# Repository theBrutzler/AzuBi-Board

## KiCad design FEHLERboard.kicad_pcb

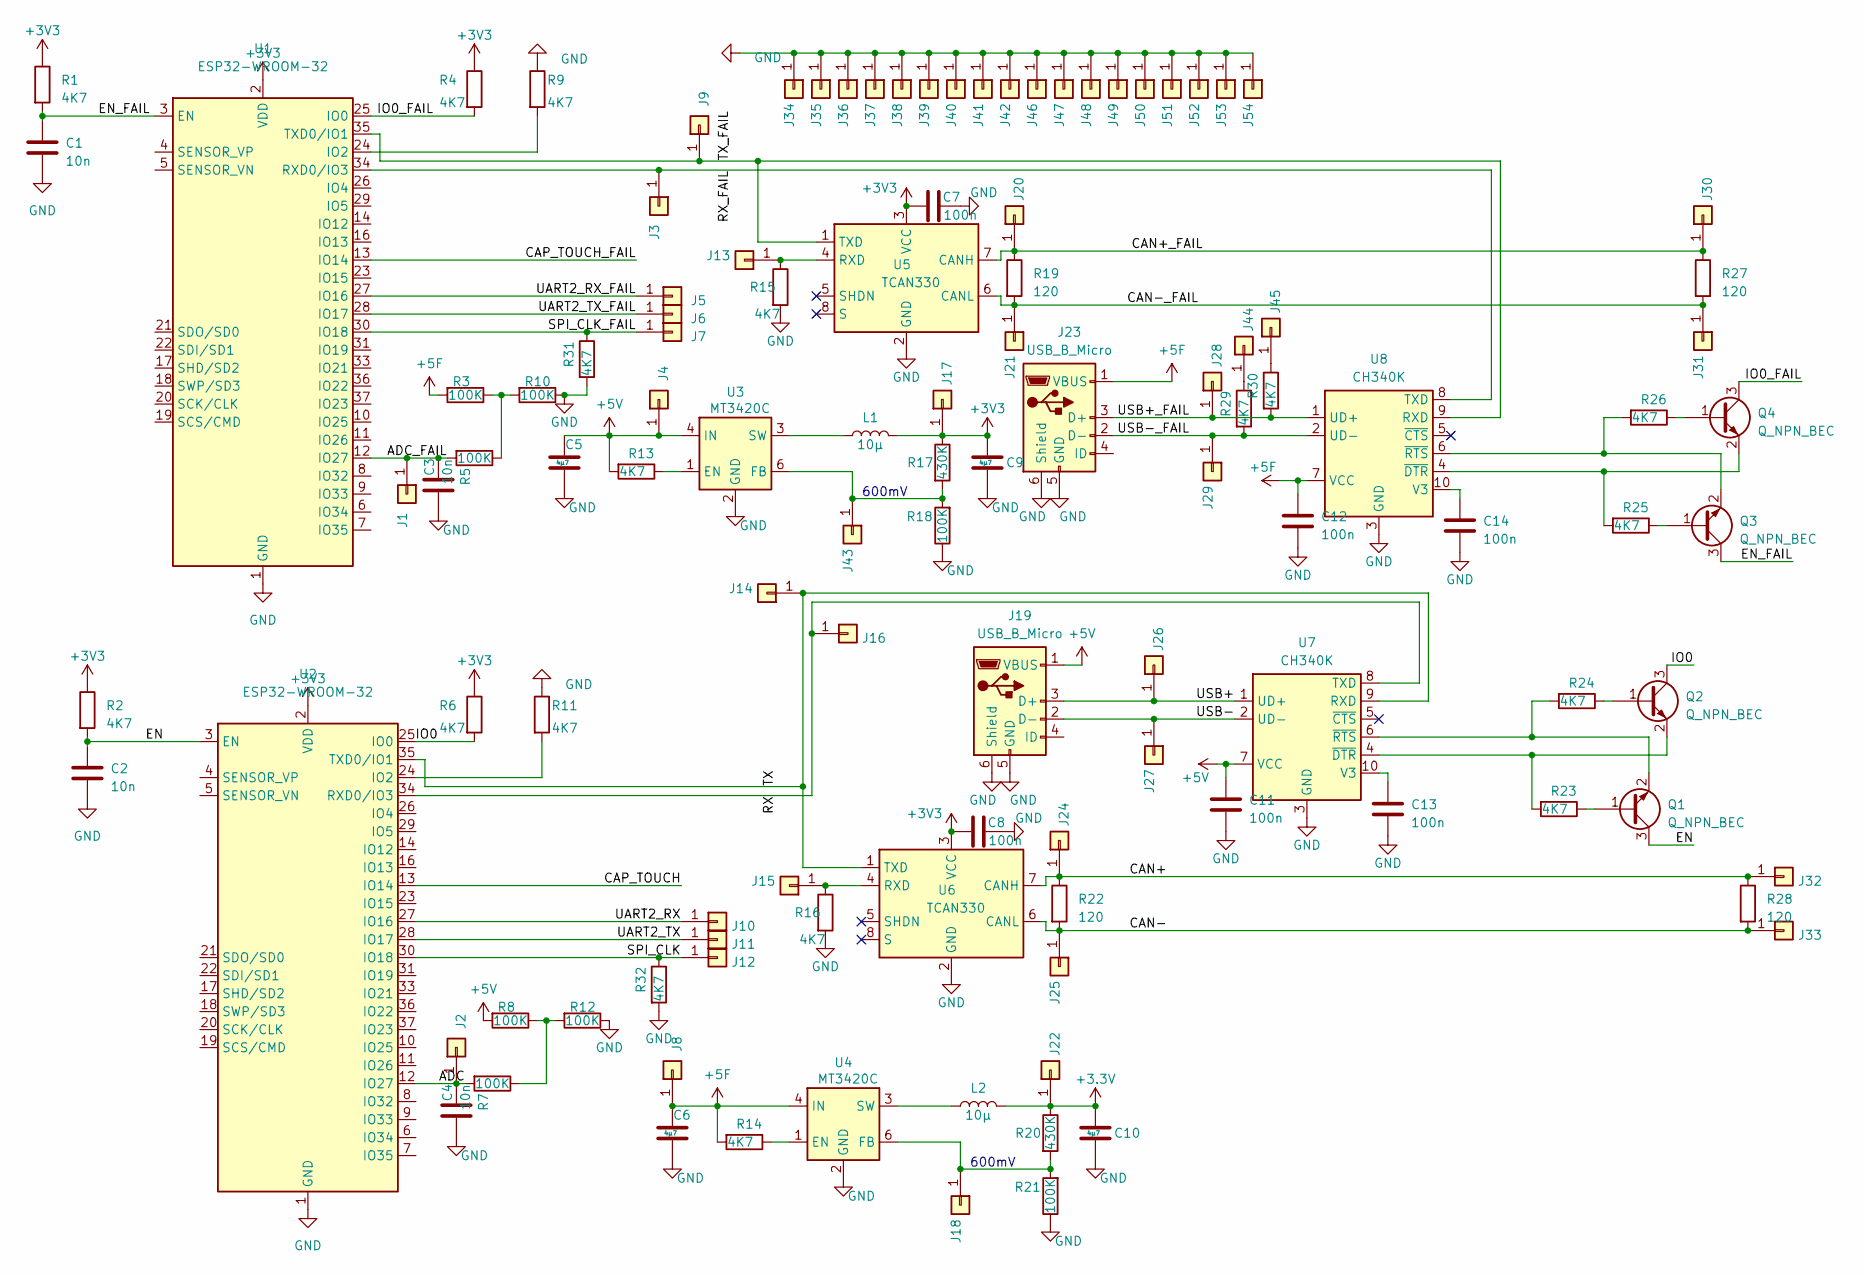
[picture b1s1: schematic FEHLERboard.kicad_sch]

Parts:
C1, C2, C3, C4: 10n; C_0603_1608Metric
C5, C6, C9, C10: 4µ7; C_0603_1608Metric; LCSC C415373
C7, C8, C11, C12, C13, C14: 100n; C_0603_1608Metric
J1, J2, J3, J4, J5, J6, J7, J8, J9, J10, J11, J12, J13, J14, J15, J16, J17, J18, J20, J21, J22, J24, J25, J26, J27, J28, J29, J30, J31, J32, J33, J43, J44, J45: Conn_01x01; TestPoint_THTPad_D1.5mm_Drill0.7mm
J19, J23: USB_B_Micro; USB_Micro-B_Amphenol_10103594-0001LF_Horizontal
J34, J35, J36, J37, J38, J39, J40, J41, J42, J46, J47, J48, J49, J50, J51, J52, J53, J54: Conn_01x01; TestPoint_THTPad_1.5x1.5mm_Drill0.7mm
L1, L2: 10µ; L_Bourns-SRN4018; LCSC C520273
Q1, Q2, Q3, Q4: Q_NPN_BEC; SOT-23; LCSC C181167
R1, R2, R4, R6, R9, R11, R15, R16: 4K7; R_0603_1608Metric
R3, R5, R7, R8, R10, R12, R18, R21: 100K; R_0603_1608Metric; LCSC C15458
R13, R14, R23, R24, R25, R26, R29, R30, R31, R32: 4K7; R_0603_1608Metric; LCSC C105428
R17, R20: 430K; R_0603_1608Metric; LCSC C170597
R19, R22, R27, R28: 120; R_0603_1608Metric
U1, U2: ESP32-WROOM-32
U3, U4: MT3420C; SOT-23-6; LCSC C181741
U5, U6: TCAN330; SOIC-8_3.9x4.9mm_P1.27mm
U7, U8: CH340K; SSOP-10_EP1_3.9x4.9mm_P1.00mm; LCSC C968586

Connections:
+5F: C6.1, C12.1, J8.1, J23.1 (VBUS), R3.2, R14.2, U4.4 (IN), U8.7 (VCC)
+5V: C5.1, C11.1, J4.1, J19.1 (VBUS), R8.2, R13.2, U3.4 (IN), U7.7 (VCC)
/ADC: C4.2, J2.1, R7.2, U2.12 (IO27)
/ADC_FAIL: C3.2, J1.1, R5.2, U1.12 (IO27)
/CAN+: J24.1, J32.1, R22.1, R28.1, U6.7 (CANH)
/CAN+_FAIL: J20.1, J30.1, R19.1, R27.1, U5.7 (CANH)
/CAN-: J25.1, J33.1, R22.2, R28.2, U6.6 (CANL)
/CAN-_FAIL: J21.1, J31.1, R19.2, R27.2, U5.6 (CANL)
/CAP_TOUCH: U2.13 (IO14)
/CAP_TOUCH_FAIL: U1.13 (IO14)
/EN: C2.1, Q1.3 (C), R2.2, U2.3 (EN)
/EN_FAIL: C1.1, Q3.3 (C), R1.2, U1.3 (EN)
/IO0: Q2.3 (C), R6.2, U2.25 (IO0)
/IO0_FAIL: Q4.3 (C), R4.2, U1.25 (IO0)
/RX: J16.1, U2.34 (RXD0/IO3), U7.8 (TXD)
/RX_FAIL: J3.1, U1.34 (RXD0/IO3), U8.8 (TXD)
/SPI_CLK: J12.1, R32.1, U2.30 (IO18)
/SPI_CLK_FAIL: J7.1, R31.1, U1.30 (IO18)
/TX: J14.1, U2.35 (TXD0/IO1), U6.1 (TXD), U7.9 (RXD)
/TX_FAIL: J9.1, U1.35 (TXD0/IO1), U5.1 (TXD), U8.9 (RXD)
/UART2_RX: J10.1, U2.27 (IO16)
/UART2_RX_FAIL: J5.1, U1.27 (IO16)
/UART2_TX: J11.1, U2.28 (IO17)
/UART2_TX_FAIL: J6.1, U1.28 (IO17)
/USB+: J19.3 (D+), J26.1, U7.1 (UD+)
/USB+_FAIL: J23.3 (D+), J28.1, R30.2, U8.1 (UD+)
/USB-: J19.2 (D-), J27.1, U7.2 (UD-)
/USB-_FAIL: J23.2 (D-), J29.1, R29.2, U8.2 (UD-)
GND: C1.2, C2.2, C3.1, C4.1, C5.2, C6.2, C7.2, C8.2, C9.2, C10.2, C11.2, C12.2, C13.2, C14.2, J19.5 (GND), J19.6 (Shield), J23.5 (GND), J23.6 (Shield), J34.1, J35.1, J36.1, J37.1, J38.1, J39.1, J40.1, J41.1, J42.1, J46.1, J47.1, J48.1, J49.1, J50.1, J51.1, J52.1, J53.1, J54.1, R9.1, R10.1, R11.1, R12.1, R15.2, R16.2, R18.1, R21.1, R31.2, R32.2, U1.1 (GND), U1.15 (GND), U1.38 (GND), U1.39 (GND), U2.1 (GND), U2.15 (GND), U2.38 (GND), U2.39 (GND), U3.2 (GND), U4.2 (GND), U5.2 (GND), U6.2 (GND), U7.3 (GND), U7.PAD (GND), U8.3 (GND), U8.PAD (GND)
unnamed: C13.1, U7.10 (V3)
unnamed: C14.1, U8.10 (V3)
unnamed: J13.1, R15.1, U5.4 (RXD)
unnamed: J15.1, R16.1, U6.4 (RXD)
unnamed: J18.1, R20.2, R21.2, U4.6 (FB)
unnamed: J43.1, R17.2, R18.2, U3.6 (FB)
unnamed: J44.1, R29.1
unnamed: J45.1, R30.1
unnamed: L1.1, U3.3 (SW)
unnamed: L2.1, U4.3 (SW)
unnamed: Q1.1 (B), R23.1
unnamed: Q1.2 (E), R24.2, U7.6 (~RTS)
unnamed: Q2.1 (B), R24.1
unnamed: Q2.2 (E), R23.2, U7.4 (~DTR)
unnamed: Q3.1 (B), R25.1
unnamed: Q3.2 (E), R26.2, U8.6 (~RTS)
unnamed: Q4.1 (B), R26.1
unnamed: Q4.2 (E), R25.2, U8.4 (~DTR)
unnamed: R9.2, U1.24 (IO2)
unnamed: R3.1, R5.1, R10.2
unnamed: R11.2, U2.24 (IO2)
unnamed: R7.1, R8.1, R12.2
unnamed: R14.1, U4.1 (EN)
unnamed: R13.1, U3.1 (EN)

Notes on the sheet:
600mV

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
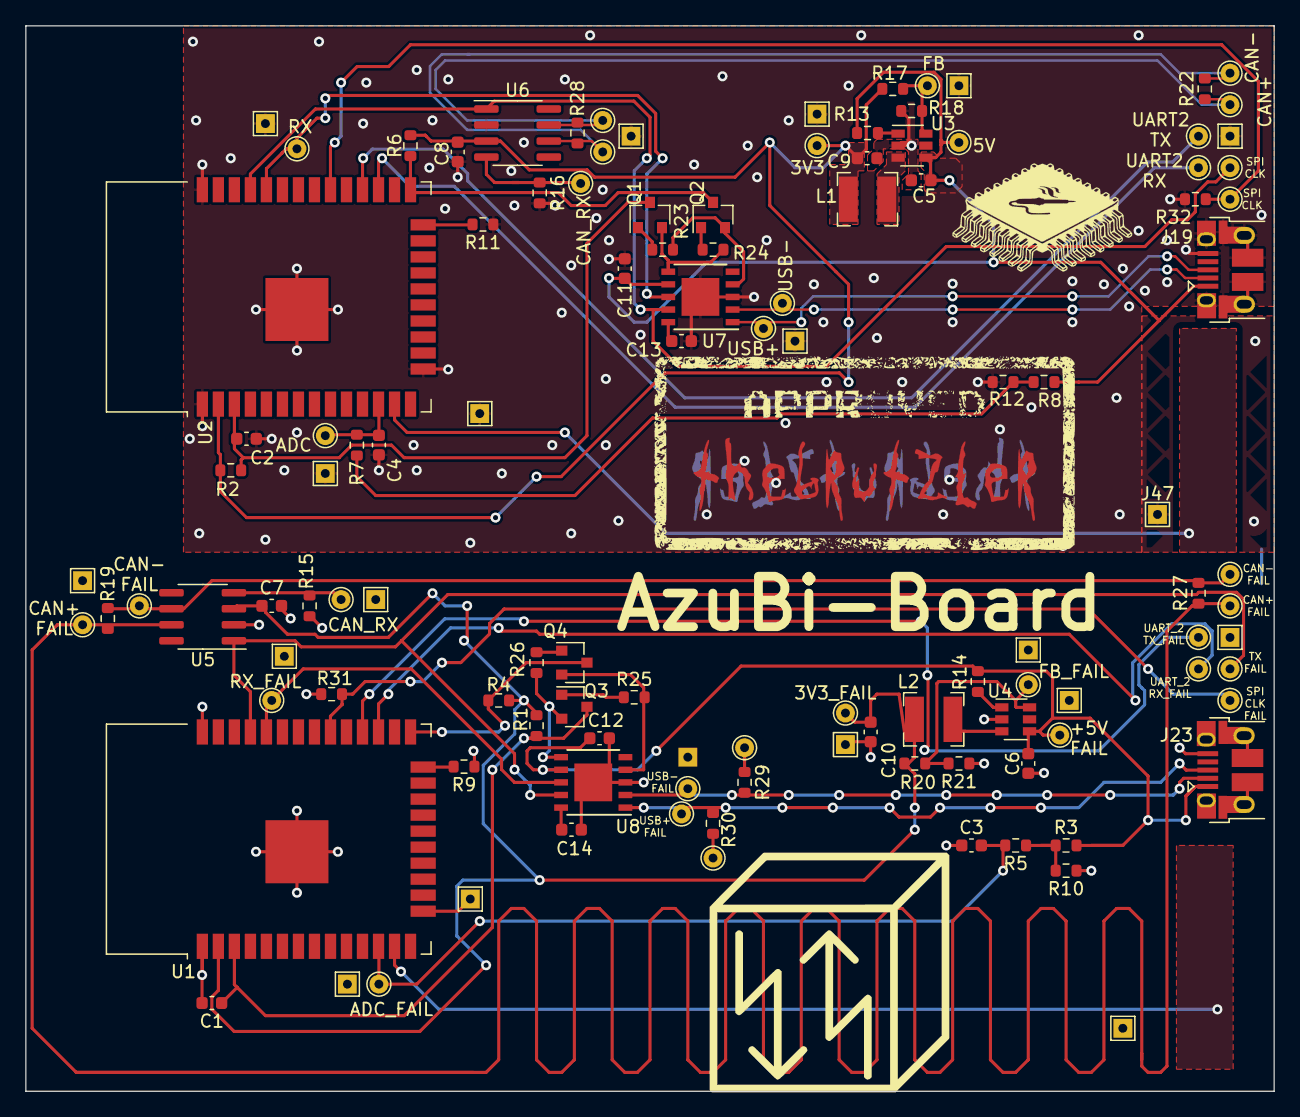
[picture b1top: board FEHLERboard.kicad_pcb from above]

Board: 2 copper layers, 99.0 x 84.5 mm, 115 parts (0 on the bottom side), 52 nets.

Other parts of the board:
J35#2: Conn_01x01; TestPoint_THTPad_1.5x1.5mm_Drill0.7mm

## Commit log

2021-08-19 Failure upgrade V2
